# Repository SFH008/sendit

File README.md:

# SendIt — Open Hardware ADC Multitool

SendIt is an open-hardware, open-firmware controller designed as a multi use tool for handling various inputs with a focus on DIY marine usage.  It runs on the Yarrboard Framework and provides a clean web UI for configuration, and multiple different APIs for accessing your data.

Built on the **ESP32-S3**, SendIt has 8 channels of 16-bit ADC with 5 different types of configurable input circuits.  With this board, each channel can be individually configured to handle these types of inputs:

* **4-20ma Transducers/Senders:** sender between +VE and GND
* **Positive Switching:** 0-32v, voltage divider acts as pulldown when NC, switch between SIGNAL and +VE
* **Negative Switching:** 1k ohm, top half of voltage divider acts as pullup, switch between SIGNAL and GND
* **0-32v:** simple voltage divider, voltage wired to SIGNAL
* **0-10k ohm:** voltage divider, external resistor wired from SIGNAL to GND
* **0-5v:** simple voltage divider, voltage wired to SIGNAL
* **Thermistor:** 0-10k ohm, wired as normal
* **Raw/Passthrough:** no extra circuitry - wire your own custom circuit

# Hardware

## Controller Board

### Core capabilities:

- ESP32-S3 module with WiFi and USB-C  
- 12–30 V DC input with onboard power regulation  
- Can be powered by USB C or external power input
- 8 x 16-bit ADC channels with 5 selectable circuits
- Selectable sensor VCC voltage for each channel (3.3v, 5v, 24v, external power)
- 30mA resettable fuse on sensor VCC
- I²C expansion (QWIIC connector)
- Unused I/O broken out as 2.54mm pin headers

### Rev C Pinout

### ADC Input Channel

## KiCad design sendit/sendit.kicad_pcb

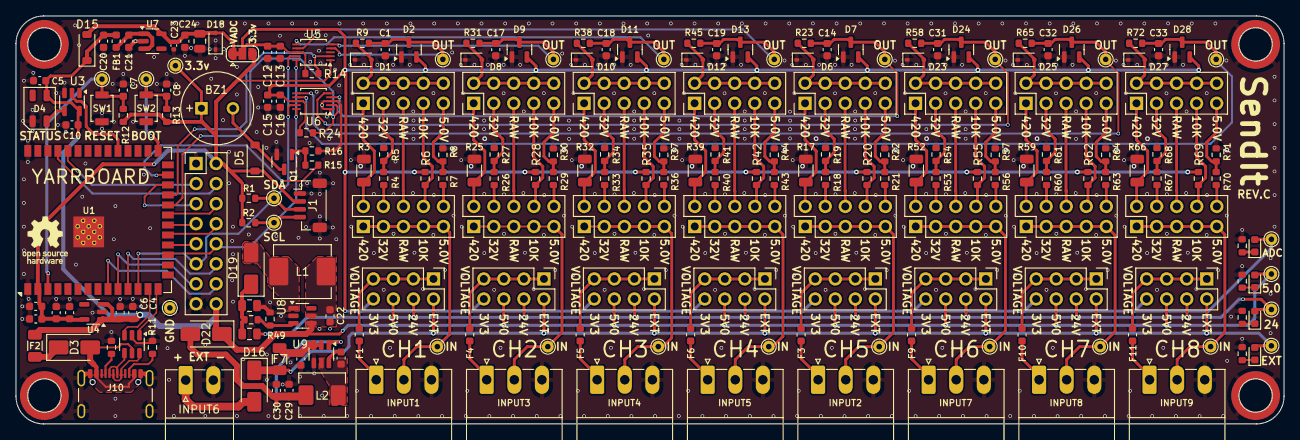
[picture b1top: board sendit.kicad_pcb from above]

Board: 4 copper layers, 160.7 x 51.7 mm, 228 parts (0 on the bottom side), 145 nets.

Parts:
BZ1: Buzzer; MagneticBuzzer_QMB-09B-03
C1, C14, C17, C18, C19, C31, C32, C33: 100nF / 50v; C_0603_1608Metric
C2, C22, C29, C30: 22uF; C_0603_1608Metric
C3, C5, C10, C12, C15, C21, C24, C28: 100nF; C_0603_1608Metric
C4, C11, C13, C16: 10uF; C_0603_1608Metric
C6, C8, C9, C20: 1uF; C_0603_1608Metric
C7: 4.7uF; C_0603_1608Metric
C23: 1nF; C_0402_1005Metric
C25: 10uF; C_0805_2012Metric
C26: 10uF / 35v; C_0603_1608Metric
C27: 22uF / 35v; C_0805_2012Metric
D1, D6, D8, D10, D12, D18, D23, D25, D27: PESD3V3L1BA,115; D_SOD-323
D2, D7, D9, D11, D13, D24, D26, D28: BAV199; SOT-23
D3, D16, D19, D22: SS36; D_SMA
D4: WS2812B-Mini; LED_WS2812B-Mini_PLCC4_3.5x3.5mm
D5: B5819W; D_SOD-123
D14, D17, D20, D21: GREEN; LED_0603_1608Metric
D15: 1N5819; D_SOD-123
F1, F3, F4, F5, F6, F9, F10, F11: 30mA / 30v; Fuse_0603_1608Metric
F2: 4A; Fuse_1206_3216Metric
F7: 500mA / 30v; Fuse_1206_3216Metric
F8: 300mA / 30v; Fuse_0805_2012Metric
FB1: BLM18AG121SN1D; L_0603_1608Metric
H1, H2, H3, H4: MountingHole_Pad; SMTSO30XXX
INPUT1, INPUT2, INPUT3, INPUT4, INPUT5, INPUT7, INPUT8, INPUT9: Conn_01x03; PhoenixContact_MC_1,5_3-G-3.5_1x03_P3.50mm_Horizontal
INPUT6: Conn_01x02; PhoenixContact_MC_1,5_2-G-3.5_1x02_P3.50mm_Horizontal
J1: Conn_01x04_MountingPin; JST_SH_BM04B-SRSS-TB_1x04-1MP_P1.00mm_Vertical
J2: Conn_02x08_Odd_Even; PinHeader_2x08_P2.54mm_Vertical
J4, J12, J19, J25, J32, J40, J47, J54: PinHeader_2x04_P2.54mm_Vertical
J6, J8, J14, J16, J21, J23, J27, J29, J34, J36, J42, J44, J49, J51, J56, J58: Conn_02x05_Odd_Even; PinHeader_2x05_P2.54mm_Vertical
J10: USB_TYPE_C_16PIN; USB_C_Receptacle_GCT_USB4105-xx-A_16P_TopMnt_Horizontal
JP1: SolderJumper_3_Bridged12; SolderJumper-3_P1.3mm_Bridged12_RoundedPad1.0x1.5mm
L1: 10uH; L_TechFuse_SL0630
L2: 4.7 uH; L_Chilisin_BMRA00050530
LOGO1: Logo_Open_Hardware_Small; OSHW-Logo_5.7x6mm_SilkScreen
Q1: AO3400A; SOT-23
R1, R2: 2.2k; R_0603_1608Metric
R3, R17, R25, R32, R39, R52, R59, R66: 100R 0.1%; R_1206_3216Metric
R4, R18, R26, R33, R40, R53, R60, R67: 28k 0.1%; R_0603_1608Metric
R5, R19, R27, R34, R41, R54, R61, R68: 2k 0.1%; R_0603_1608Metric
R6, R8, R20, R22, R28, R30, R35, R37, R42, R44, R49, R55, R57, R62, R64, R69, R71: 10k 0.1%; R_0603_1608Metric
R7, R21, R29, R36, R43, R56, R63, R70: 18k 0.1%; R_0603_1608Metric
R9, R23, R31, R38, R45, R58, R65, R72: 1k; R_0603_1608Metric
R10, R11, R50: 5.1k; R_0603_1608Metric
R12, R13, R14, R24, R46: 10k; R_0603_1608Metric
R15: 100R; R_0603_1608Metric
R16, R47, R51: 100k; R_0603_1608Metric
R48: 390K 1%; R_0603_1608Metric
SW1: RESET; SW_SPST_B3U-1000P
SW2: BOOT; SW_SPST_B3U-1000P
TP1, TP2, TP5, TP6, TP7, TP16, TP17, TP18, TP19, TP20: TestPoint_THTPad_D1.5mm_Drill0.7mm
TP3, TP4, TP8, TP9, TP10, TP11, TP12, TP13, TP14, TP15, TP21, TP22, TP23, TP24, TP25, TP26: TestPoint; TestPoint_THTPad_D1.5mm_Drill0.7mm
U1: ESP32-S3-WROOM-1-N16R8; ESP32-S3-WROOM-1
U2: USBLC6-2SC6; SOT-23-6
U3: SN74LV1T34DBV; SOT-23-5
U4: XC6210B332MR; SOT-23-5
U5, U6: ADS1115IDGSR; TSSOP-10_3x3mm_P0.5mm
U7: TPS7A2033PDBVR; SOT-23-5
U8: MT3608; SOT-23-6
U9: AP63205WU; TSOT-23-6

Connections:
+3.3V: BZ1.1 (+), C2.1, C3.1, C9.1, C11.1, D5.1 (K), J1.2, J2.2, JP1.3 (B), R1.2, R2.2, R12.1, R13.2, TP7.1, U1.2 (3V3), U4.5 (VOUT), U5.1 (ADDR)
+3.3VADC: C12.1, C13.1, C15.1, C16.1, D2.2 (K), D7.2 (K), D9.2 (K), D11.2 (K), D13.2 (K), D20.2 (A), D24.2 (K), D26.2 (K), D28.2 (K), J4.8, J12.8, J19.8, J25.8, J32.8, J40.8, J47.8, J54.8, JP1.2 (C), R6.2, R14.1, R20.2, R24.1, R28.2, R35.2, R42.2, R55.2, R62.2, R69.2, TP19.1, U5.8 (VDD), U6.8 (VDD)
+5V: C4.1, C5.1, C6.1, C10.1, C20.1, C22.1, D4.1 (VDD), D14.2 (A), D15.1 (K), D22.1 (K), F2.2, FB1.1, J2.16, J4.6, J12.6, J19.6, J25.6, J32.6, J40.6, J47.6, J54.6, L1.1, TP16.1, U3.5 (VCC), U4.1 (VIN), U4.3 (CE), U8.4 (EN), U8.5 (IN)
+24V: D21.2 (A), F8.1, J4.4, J12.4, J19.4, J25.4, J32.4, J40.4, J47.4, J54.4, TP20.1
/ADC1/ADC0: C1.1, D2.3 (COM), R9.2, TP4.1, U5.4 (AIN0)
/ADC1/ADC1: C17.1, D9.3 (COM), R31.2, TP11.1, U5.5 (AIN1)
/ADC1/ADC2: C18.1, D11.3 (COM), R38.2, TP13.1, U5.6 (AIN2)
/ADC1/ADC3: C19.1, D13.3 (COM), R45.2, TP15.1, U5.7 (AIN3)
/ADC2/ADC0: C14.1, D7.3 (COM), R23.2, TP9.1, U6.4 (AIN0)
/ADC2/ADC1: C31.1, D24.3 (COM), R58.2, TP22.1, U6.5 (AIN1)
/ADC2/ADC2: C32.1, D26.3 (COM), R65.2, TP24.1, U6.6 (AIN2)
/ADC2/ADC3: C33.1, D28.3 (COM), R72.2, TP26.1, U6.7 (AIN3)
/ESP32-S3/CC1_1: J10.A5 (CC1), R10.1
/ESP32-S3/CC2_1: J10.B5 (CC2), R11.1
/ESP32-S3/EN: C7.1, R12.2, SW1.1, TP5.1, U1.3 (EN)
/ESP32-S3/ESP_USB+: U1.14 (USB_D+), U2.1 (I/O1)
/ESP32-S3/ESP_USB-: U1.13 (USB_D-), U2.3 (I/O2)
/ESP32-S3/GPIO0_BOOT: C8.2, R13.1, SW2.1, TP6.1, U1.27 (IO0)
/ESP32-S3/GPIO38: U1.31 (IO38), U3.2 (A)
/ESP32-S3/GPIO48: R15.2, U1.25 (IO48)
/ESP32-S3/USB_D+: J10.A6 (D+), J10.B6 (D+), U2.6 (I/O1)
/ESP32-S3/USB_D-: J10.A7 (D-), J10.B7 (D-), U2.4 (I/O2)
/ESP32-S3/VBUS: D3.2 (A), J10.A4 (VBUS), J10.A9 (VBUS), J10.B4 (VBUS), J10.B9 (VBUS), U2.5 (VBUS)
/Power Supply/bst: C28.2, U9.6 (BST)
/Power Supply/sw_node: C28.1, L2.1, U9.5 (SW)
ADC_ALERT/RDY1: R14.2, U1.23 (IO21), U5.2 (ALERT/RDY)
ADC_ALERT/RDY2: R24.2, U1.22 (IO14), U6.2 (ALERT/RDY)
ESP_RX0: J2.3, U1.36 (RXD0)
ESP_TX0: J2.4, U1.37 (TXD0)
GND: C1.2, C2.2, C3.2, C4.2, C5.2, C6.2, C7.2, C8.1, C9.2, C10.2, C11.2, C12.2, C13.2, C14.2, C15.2, C16.2, C17.2, C18.2, C19.2, C20.2, C21.2, C22.2, C23.2, C24.2, C25.2, C26.2, C27.2, C29.2, C30.2, C31.2, C32.2, C33.2, D1.1 (A1), D2.1 (A), D4.3 (VSS), D6.1 (A1), D7.1 (A), D8.1 (A1), D9.1 (A), D10.1 (A1), D11.1 (A), D12.1 (A1), D13.1 (A), D18.1 (A1), D23.1 (A1), D24.1 (A), D25.1 (A1), D26.1 (A), D27.1 (A1), D28.1 (A), H1.1, H2.1, H3.1, H4.1, INPUT1.3, INPUT2.3, INPUT3.3, INPUT4.3, INPUT5.3, INPUT6.2, INPUT7.3, INPUT8.3, INPUT9.3, J1.1, J1.MP (MountPin), J2.1, J2.15, J10.A1 (GND), J10.A12 (GND), J10.B1 (GND), J10.B12 (GND), J10.S1 (SHIELD), Q1.2 (S), R3.1, R5.1, R8.1, R10.2, R11.2, R16.2, R17.1, R19.1, R22.1, R25.1, R27.1, R30.1, R32.1, R34.1, R37.1, R39.1, R41.1, R44.1, R46.2, R47.2, R49.2, R50.2, R51.2, R52.1, R54.1, R57.1, R59.1, R61.1, R64.1, R66.1, R68.1, R71.1, SW1.2, SW2.2, TP17.1, U1.1 (GND), U1.40 (GND), U1.41 (GND), U2.2 (GND), U3.3 (GND), U4.2 (GND), U5.3 (GND), U6.1 (ADDR), U6.3 (GND), U7.2 (GND), U8.2 (GND), U9.4 (GND)
GPIO10: J2.9, U1.18 (IO10)
GPIO11: J2.8, U1.19 (IO11)
GPIO12: J2.7, U1.20 (IO12)
GPIO13: J2.6, U1.21 (IO13)
GPIO16: J2.14, U1.9 (IO16)
GPIO17: J2.13, U1.10 (IO17)
GPIO18: J2.12, U1.11 (IO18)
GPIO47: J2.5, U1.24 (IO47)
unnamed: BZ1.2 (-), D5.2 (A), Q1.3 (D)
unnamed: D1.2 (A2), J8.2, J8.4, J8.6, J8.8, J8.10, R9.1
unnamed: D3.1 (K), F2.1
unnamed: D4.4 (DIN), U3.4 (Y)
unnamed: D6.2 (A2), J16.2, J16.4, J16.6, J16.8, J16.10, R23.1
unnamed: D8.2 (A2), J23.2, J23.4, J23.6, J23.8, J23.10, R31.1
unnamed: D10.2 (A2), J29.2, J29.4, J29.6, J29.8, J29.10, R38.1
unnamed: D12.2 (A2), J36.2, J36.4, J36.6, J36.8, J36.10, R45.1
unnamed: D14.1 (K), R46.1
unnamed: C23.1, C24.1, C25.1, D15.2 (A), D18.2 (A2), JP1.1 (A), U7.5 (OUT)
unnamed: D16.2 (A), INPUT6.1
unnamed: D17.1 (K), R47.1
unnamed: D19.2 (A), L1.2, U8.1 (SW)
unnamed: C27.1, D19.1 (K), F8.2, R48.1
unnamed: D20.1 (K), R50.1
unnamed: D21.1 (K), R51.1
unnamed: C29.1, C30.1, D22.2 (A), L2.2, U9.1 (FB)
unnamed: D23.2 (A2), J44.2, J44.4, J44.6, J44.8, J44.10, R58.1
unnamed: D25.2 (A2), J51.2, J51.4, J51.6, J51.8, J51.10, R65.1
unnamed: D27.2 (A2), J58.2, J58.4, J58.6, J58.8, J58.10, R72.1
unnamed: F1.2, INPUT1.1
unnamed: INPUT1.2, J6.1, J6.3, J6.5, J6.7, J6.9, TP3.1
unnamed: F3.2, INPUT2.1
unnamed: INPUT2.2, J14.1, J14.3, J14.5, J14.7, J14.9, TP8.1
unnamed: F4.2, INPUT3.1
unnamed: INPUT3.2, J21.1, J21.3, J21.5, J21.7, J21.9, TP10.1
unnamed: F5.2, INPUT4.1
unnamed: INPUT4.2, J27.1, J27.3, J27.5, J27.7, J27.9, TP12.1
unnamed: F6.2, INPUT5.1
unnamed: INPUT5.2, J34.1, J34.3, J34.5, J34.7, J34.9, TP14.1
unnamed: F9.2, INPUT7.1
unnamed: INPUT7.2, J42.1, J42.3, J42.5, J42.7, J42.9, TP21.1
unnamed: F10.2, INPUT8.1
unnamed: INPUT8.2, J49.1, J49.3, J49.5, J49.7, J49.9, TP23.1
unnamed: F11.2, INPUT9.1
unnamed: INPUT9.2, J56.1, J56.3, J56.5, J56.7, J56.9, TP25.1
unnamed: F1.1, J4.1, J4.3, J4.5, J4.7
unnamed: J6.2, J8.1, R3.2
unnamed: J6.4, R4.2
unnamed: J6.6, J8.5
unnamed: J6.8, J8.7, R6.1
unnamed: J6.10, R7.2
unnamed: J8.3, R4.1, R5.2
unnamed: J8.9, R7.1, R8.2
unnamed: F3.1, J12.1, J12.3, J12.5, J12.7
unnamed: J14.2, J16.1, R17.2
unnamed: J14.4, R18.2
unnamed: J14.6, J16.5
unnamed: J14.8, J16.7, R20.1
unnamed: J14.10, R21.2
unnamed: J16.3, R18.1, R19.2
unnamed: J16.9, R21.1, R22.2
unnamed: F4.1, J19.1, J19.3, J19.5, J19.7
unnamed: J21.2, J23.1, R25.2
unnamed: J21.4, R26.2
unnamed: J21.6, J23.5
unnamed: J21.8, J23.7, R28.1
unnamed: J21.10, R29.2
unnamed: J23.3, R26.1, R27.2
unnamed: J23.9, R29.1, R30.2
unnamed: F5.1, J25.1, J25.3, J25.5, J25.7
unnamed: J27.2, J29.1, R32.2
unnamed: J27.4, R33.2
unnamed: J27.6, J29.5
unnamed: J27.8, J29.7, R35.1
unnamed: J27.10, R36.2
unnamed: J29.3, R33.1, R34.2
unnamed: J29.9, R36.1, R37.2
unnamed: F6.1, J32.1, J32.3, J32.5, J32.7
unnamed: J34.2, J36.1, R39.2
unnamed: J34.4, R40.2
unnamed: J34.6, J36.5
unnamed: J34.8, J36.7, R42.1
unnamed: J34.10, R43.2
unnamed: J36.3, R40.1, R41.2
unnamed: J36.9, R43.1, R44.2
unnamed: F9.1, J40.1, J40.3, J40.5, J40.7
unnamed: J42.2, J44.1, R52.2
unnamed: J42.4, R53.2
unnamed: J42.6, J44.5
unnamed: J42.8, J44.7, R55.1
unnamed: J42.10, R56.2
unnamed: J44.3, R53.1, R54.2
unnamed: J44.9, R56.1, R57.2
unnamed: F10.1, J47.1, J47.3, J47.5, J47.7
unnamed: J49.2, J51.1, R59.2
unnamed: J49.4, R60.2
unnamed: J49.6, J51.5
unnamed: J49.8, J51.7, R62.1
unnamed: J49.10, R63.2
unnamed: J51.3, R60.1, R61.2
unnamed: J51.9, R63.1, R64.2
unnamed: F11.1, J54.1, J54.3, J54.5, J54.7
unnamed: J56.2, J58.1, R66.2
unnamed: J56.4, R67.2
unnamed: J56.6, J58.5
unnamed: J56.8, J58.7, R69.1
unnamed: J56.10, R70.2
unnamed: J58.3, R67.1, R68.2
unnamed: J58.9, R70.1, R71.2
unnamed: Q1.1 (G), R15.1, R16.1
unnamed: C21.1, FB1.2, U7.1 (IN), U7.3 (EN)
unnamed: R48.2, R49.1, U8.3 (FB)
unnamed: C26.1, F7.2, U9.2 (EN), U9.3 (IN)
SCL: J1.4, J2.10, R2.1, TP2.1, U1.17 (IO9), U5.10 (SCL), U6.10 (SCL)
SDA: J1.3, J2.11, R1.1, TP1.1, U1.12 (IO8), U5.9 (SDA), U6.9 (SDA)
VEXT: D16.1 (K), D17.2 (A), F7.1, J4.2, J12.2, J19.2, J25.2, J32.2, J40.2, J47.2, J54.2, TP18.1

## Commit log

2025-03-17 big update on the potential design.
2025-03-19 bigger update
2025-03-19 cleaned up the dir.
2025-03-19 changed from mux to pin jumpers
2025-07-30 layout work.
2025-07-30 first pass layout finished.
2025-07-30 finished layout and routing
2025-08-07 updated footprints and lcsc numbers.
2025-08-14 updated todo
2025-08-15 added fuses, 24v filters, and indicator leds.
2025-08-15 test run of jlcpcb upload looks good.
2025-08-15 fully routed again.
2025-08-15 passed erc and drc
2025-08-15 added shunts to the BOM
2025-08-15 switch to test points with drilled holes.
2025-08-15 added alert lines
2025-08-15 changed inductor on 24v circuit, cleaned up board a bit.
2025-08-15 Rev-A ready for production
2025-08-15 Rev-A sent to production.
2025-10-01 big schematic rework for Rev B
2025-10-02 ready for routing
2025-10-02 brought over the latest esp32-s3 schematic
2025-10-02 piezo resistor
2025-10-02 first pass fully routed
2025-10-02 passing erc and drc
2025-10-03 silkscreen updated, looking good.
2025-10-03 ground plane / via stitching done
2025-10-03 bom and placement looking good.
2025-10-03 some final resistor value tweaking
2025-10-04 cleaning up schematics a bit for design review
2025-10-07 sent rev b to production
2025-10-08 case design finished
2025-10-08 added schematic and case
2025-11-06 updated plan for rev c
2025-11-07 started work on the rev c schematic
2025-11-08 more work on rev c board schematic
2025-11-08 most of the work on the schematic is done.
2025-11-10 more work towards rev c board.
2025-11-12 more rev c progress
2025-11-12 power system work and layout
2025-11-13 big change removing the usb hub and serial chip.
2025-11-13 big routing push
2025-11-13 first pass fully routed.
2025-11-13 finished extra pin selection + routing
2025-11-13 beefed up the 24v to 5v circuit
2025-11-13 fixed erc errors
2025-11-13 drc + silkscreen
2025-11-13 a couple more silkscreen tweaks
2025-11-13 via stitching and calculations
2025-11-14 double checked power supplies + gave esp32-s3 proper voltage/ground symbols
2025-11-14 fixed spacer footprint
2025-11-14 all footprints have 3d models now
2025-11-14 moved the dc buck circuit away from the usb port.
2025-11-14 some bom work
2025-11-15 added diode to prevent backfeed into 24v buck and beefed up 5v rail
2025-11-29 added pullup resistors to ads1115 alert line
2025-11-29 updated changelog and production file tweak
2025-12-01 fixed some silkscreen errors and added visas before submitting Rev C2 design
2025-12-01 re-added reference designator for pullups
2026-01-23 added rev c pinout diagram
2026-01-23 added rev c pinout and basic readme
